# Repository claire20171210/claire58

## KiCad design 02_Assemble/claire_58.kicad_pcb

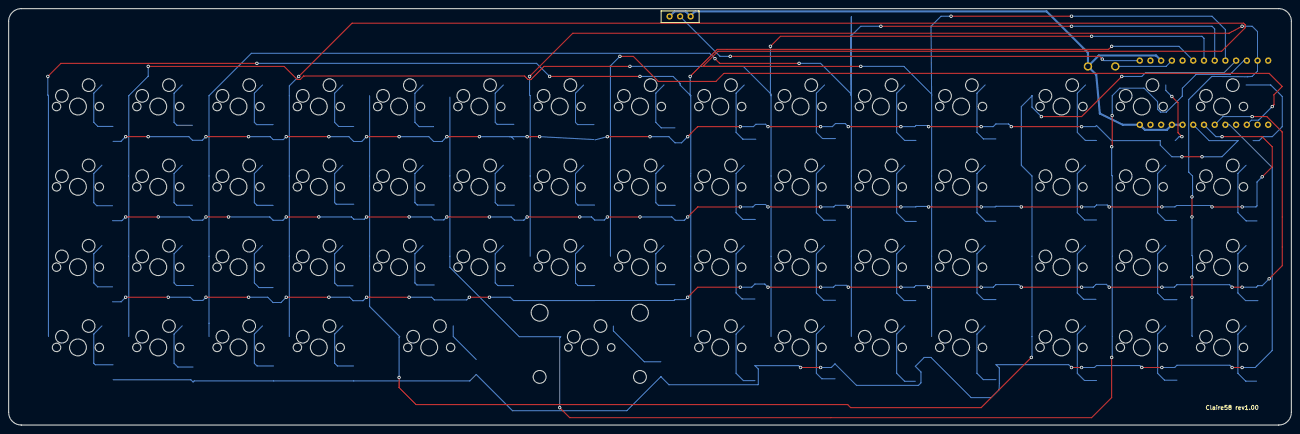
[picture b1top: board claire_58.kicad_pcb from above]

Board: 2 copper layers, 304.4 x 98.8 mm, 119 parts (0 on the bottom side), 73 nets.

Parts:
D1, D2, D3, D4, D5, D6, D7, D8, D9, D10, D11, D12, D13, D14, D15, D16, D17, D18, D19, D20, D21, D22, D23, D24, D25, D26, D27, D28, D29, D30, D31, D32, D33, D34, D35, D36, D37, D38, D39, D40, D41, D42, D43, D44, D45, D46, D47, D48, D49, D50, D51, D52, D53, D54, D55, D56, D57, D58: D; Diode_SMD
J1: Conn_01x02; Battery_XH2.5_GL_PCB
SW1, SW2, SW3, SW4, SW5, SW6, SW7, SW8, SW9, SW10, SW11, SW12, SW13, SW14, SW15, SW16, SW17, SW18, SW19, SW21, SW22, SW23, SW25, SW26, SW27, SW28, SW29, SW30, SW31, SW32, SW33, SW34, SW35, SW36, SW37, SW38, SW39, SW40, SW41, SW42, SW43, SW44, SW45, SW46, SW47, SW48, SW49, SW50, SW52, SW53, SW54, SW56, SW57, SW58: SW_PUSH; CherryMX_Hotswap_1.0u
SW20: SW_PUSH; CherryMX_Hotswap_1.75u
SW24: SW_PUSH; CherryMX_Hotswap_2.25u_Rev
SW51, SW55: SW_PUSH; CherryMX_Hotswap_1.0u_Small1
SW59: SW_PUSH; ResetSW
U1: BLEMicroPro; Micon_BMP_GL

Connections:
Bat+: J1.1, U1.25
Col0: SW1.1, SW2.1, SW3.1, SW4.1, SW31.1, SW32.1, SW33.1, SW34.1, U1.20
Col1: SW5.1, SW6.1, SW7.1, SW8.1, SW35.1, SW36.1, SW37.1, SW38.1, U1.19
Col2: SW9.1, SW10.1, SW11.1, SW12.1, SW39.1, SW40.1, SW41.1, SW42.1, U1.18
Col3: SW13.1, SW14.1, SW15.1, SW16.1, SW43.1, SW44.1, SW45.1, SW46.1, U1.17
Col4: SW17.1, SW18.1, SW19.1, SW20.1, SW47.1, SW48.1, SW49.1, SW50.1, U1.16
Col5: SW21.1, SW22.1, SW23.1, SW24.1, SW51.1, SW52.1, SW53.1, SW54.1, U1.15
Col6: SW25.1, SW26.1, SW27.1, SW55.1, SW56.1, SW57.1, SW58.1, U1.14
Col7: SW28.1, SW29.1, SW30.1, U1.10
GND: J1.2, SW59.2, U1.3, U1.4, U1.23, U1.26
unnamed: D1.2, SW1.2
unnamed: D2.2, SW2.2
unnamed: D3.2, SW3.2
unnamed: D4.2, SW4.2
unnamed: D5.2, SW5.2
unnamed: D6.2, SW6.2
unnamed: D7.2, SW7.2
unnamed: D8.2, SW8.2
unnamed: D9.2, SW9.2
unnamed: D10.2, SW10.2
unnamed: D11.2, SW11.2
unnamed: D12.2, SW12.2
unnamed: D13.2, SW13.2
unnamed: D14.2, SW14.2
unnamed: D15.2, SW15.2
unnamed: D16.2, SW16.2
unnamed: D17.2, SW17.2
unnamed: D18.2, SW18.2
unnamed: D19.2, SW19.2
unnamed: D20.2, SW20.2
unnamed: D21.2, SW21.2
unnamed: D22.2, SW22.2
unnamed: D23.2, SW23.2
unnamed: D24.2, SW24.2
unnamed: D25.2, SW25.2
unnamed: D26.2, SW26.2
unnamed: D27.2, SW27.2
unnamed: D28.2, SW28.2
unnamed: D29.2, SW29.2
unnamed: D30.2, SW30.2
unnamed: D31.1, SW31.2
unnamed: D32.1, SW32.2
unnamed: D33.1, SW33.2
unnamed: D34.1, SW34.2
unnamed: D35.1, SW35.2
unnamed: D36.1, SW36.2
unnamed: D37.1, SW37.2
unnamed: D38.1, SW38.2
unnamed: D39.1, SW39.2
unnamed: D40.1, SW40.2
unnamed: D41.1, SW41.2
unnamed: D42.1, SW42.2
unnamed: D43.1, SW43.2
unnamed: D44.1, SW44.2
unnamed: D45.1, SW45.2
unnamed: D46.1, SW46.2
unnamed: D47.1, SW47.2
unnamed: D48.1, SW48.2
unnamed: D49.1, SW49.2
unnamed: D50.1, SW50.2
unnamed: D51.1, SW51.2
unnamed: D52.1, SW52.2
unnamed: D53.1, SW53.2
unnamed: D54.1, SW54.2
unnamed: D55.1, SW55.2
unnamed: D56.1, SW56.2
unnamed: D57.1, SW57.2
unnamed: D58.1, SW58.2
Reset: SW59.1, U1.22
Row0: D1.1, D5.1, D9.1, D13.1, D17.1, D21.1, D25.1, D28.1, D31.2, D35.2, D39.2, D43.2, D47.2, D51.2, D55.2, U1.5
Row1: D2.1, D6.1, D10.1, D14.1, D18.1, D22.1, D26.1, D29.1, D32.2, D36.2, D40.2, D44.2, D48.2, D52.2, D56.2, U1.6
Row2: D3.1, D7.1, D11.1, D15.1, D19.1, D23.1, D27.1, D30.1, D33.2, D37.2, D41.2, D45.2, D49.2, D53.2, D57.2, U1.7
Row3: D4.1, D8.1, D12.1, D16.1, D20.1, D24.1, D34.2, D38.2, D42.2, D46.2, D50.2, D54.2, D58.2, U1.8
